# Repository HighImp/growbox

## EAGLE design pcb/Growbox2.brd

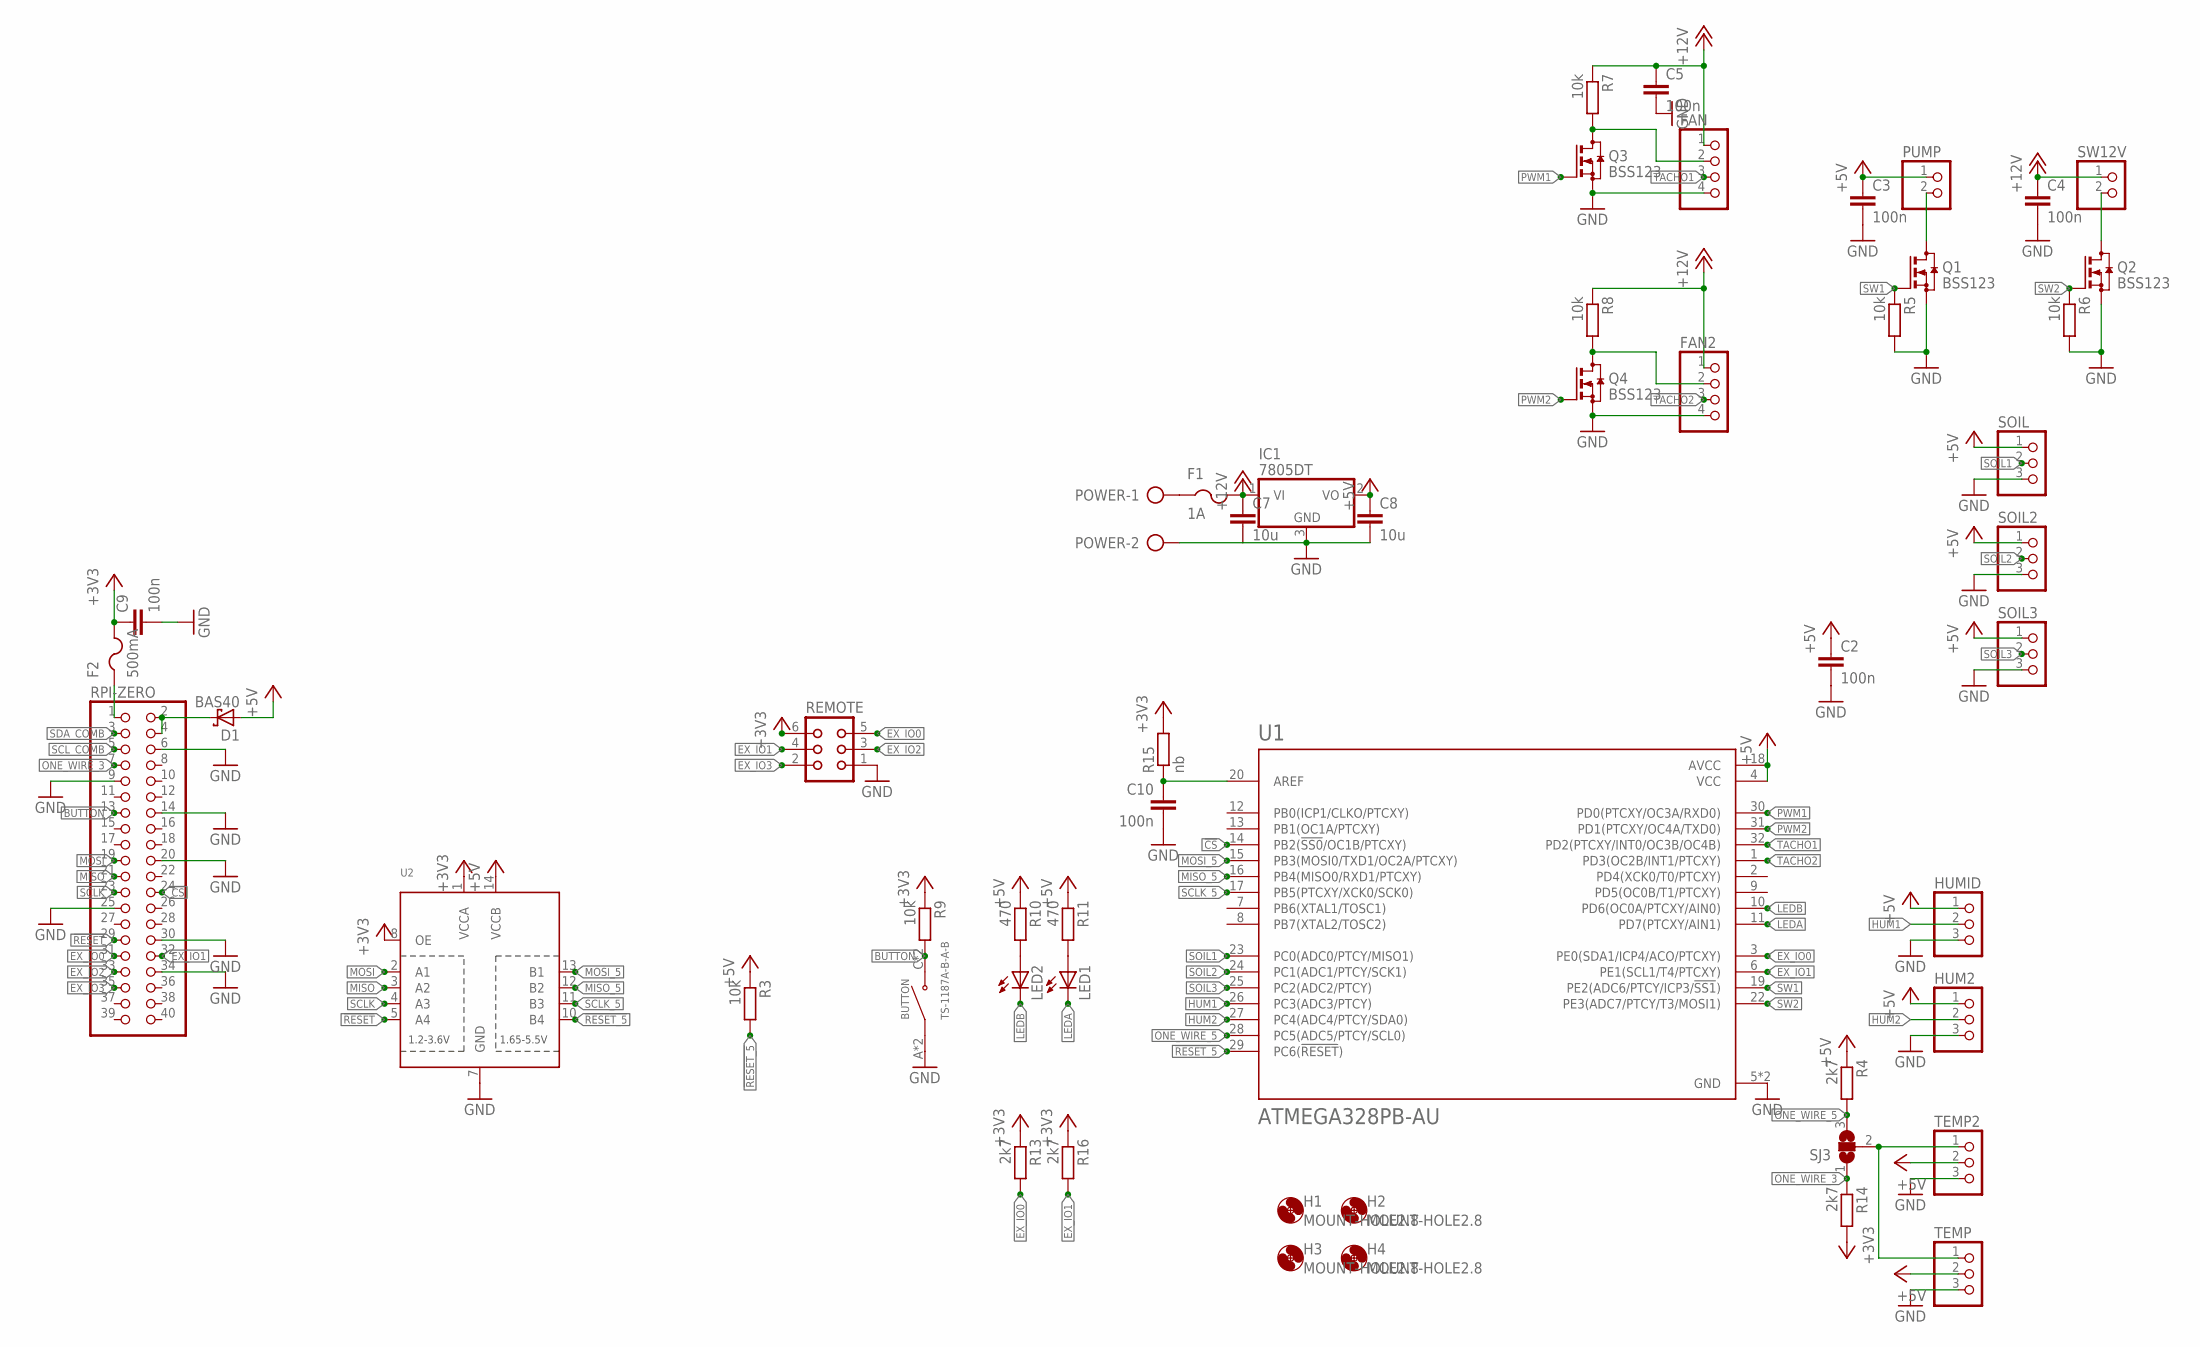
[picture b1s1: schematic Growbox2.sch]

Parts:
BUTTON: TS-1187A-B-A-B; SW_TS-1187A-B-A-B
C2, C3, C4, C5, C9, C10: 100n; C0603
C7, C8: 10u; C0603
D1: BAS40; SOT23
F1: 1A; R1206
F2: 500mA; R1206
FAN, FAN2: PINHD-1X4; 1X04
H1, H2, H3, H4: MOUNT-HOLE2.8; 2,8
HUM2: PINHD-1X3; 1X03
HUMID: PINHD-1X3; 1X03
IC1: 7805DT; TO252
LED1, LED2: LEDCHIP-LED0603; CHIP-LED0603
POWER: AK300/2
PUMP: PINHD-1X2; 1X02
Q1, Q2, Q3, Q4: BSS123; SOT23
R3, R5, R6, R7, R8, R9: 10k; R0603
R4, R13, R14, R16: 2k7; R0603
R10, R11: 470; R0603
R15: nb; R0603
REMOTE: CON06
RPI-ZERO: PINHD-2X20; 2X20
SJ3: SJ2W; SJ_2
SOIL, SOIL2, SOIL3: PINHD-1X3; 1X03
SW12V: PINHD-1X2; 1X02
TEMP, TEMP2: PINHD-1X3; 1X03
U1: ATMEGA328PB-AU; QFP80P900X900X120-32N
U2: TXB0104PWR; TSSOP14

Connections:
!CS: RPI-ZERO.24, U1.14 (PB2(!SS0!/OC1B/PTCXY))
!RESET: RPI-ZERO.29, U2.5 (A4)
!RESET_5: R3.2, U1.29 (PC6(!RESET!)), U2.10 (B4)
+3V3: C9.1, F2.2, R9.1, R13.1, R14.2, R15.2, R16.1, REMOTE.6, U2.1 (VCCA), U2.8 (OE)
+5V: C2.1, C3.1, C8.1, D1.1 (A), HUM2.1, HUMID.1, IC1.2 (VO), PUMP.1, R3.1, R4.1, R10.1, R11.1, SOIL.1, SOIL2.1, SOIL3.1, TEMP.2, TEMP2.2, U1.4 (VCC), U1.18 (AVCC), U2.14 (VCCB)
+12V: C4.1, C5.1, C7.1, F1.2, FAN.1, FAN2.1, IC1.1 (VI), R7.1, R8.1, SW12V.1
AREF: C10.1, R15.1, U1.20 (AREF)
BUTTON: BUTTON.C (NO), BUTTON.D (NO), R9.2, RPI-ZERO.13
EX_IO0: R13.2, REMOTE.5, RPI-ZERO.31, U1.3 (PE0(SDA1/ICP4/ACO/PTCXY))
EX_IO1: R16.2, REMOTE.4, RPI-ZERO.32, U1.6 (PE1(SCL1/T4/PTCXY))
EX_IO2: REMOTE.3, RPI-ZERO.33
EX_IO3: REMOTE.2, RPI-ZERO.35
GND: BUTTON.A (COM), BUTTON.B (COM), C2.2, C3.2, C4.2, C5.2, C7.2, C8.2, C9.2, C10.2, FAN.4, FAN2.4, HUM2.3, HUMID.3, IC1.3 (GND), POWER.2, Q1.2 (S), Q2.2 (S), Q3.2 (S), Q4.2 (S), R5.2, R6.2, REMOTE.1, RPI-ZERO.6, RPI-ZERO.9, RPI-ZERO.14, RPI-ZERO.20, RPI-ZERO.25, RPI-ZERO.30, RPI-ZERO.34, SOIL.3, SOIL2.3, SOIL3.3, TEMP.3, TEMP2.3, U1.5 (GND), U1.21 (GND), U2.7 (GND)
HUM1: HUMID.2, U1.26 (PC3(ADC3/PTCY))
HUM2: HUM2.2, U1.27 (PC4(ADC4/PTCY/SDA0))
LEDA: LED1.C, U1.11 (PD7(PTCXY/AIN1))
LEDB: LED2.C, U1.10 (PD6(OC0A/PTCXY/AIN0))
MISO: RPI-ZERO.21, U2.3 (A2)
MISO_5: U1.16 (PB4(MISO0/RXD1/PTCXY)), U2.12 (B2)
MOSI: RPI-ZERO.19, U2.2 (A1)
MOSI_5: U1.15 (PB3(MOSI0/TXD1/OC2A/PTCXY)), U2.13 (B1)
unnamed: F1.1, POWER.1
unnamed: F2.1, RPI-ZERO.1
unnamed: LED2.A, R10.2
unnamed: D1.3 (C), RPI-ZERO.2, RPI-ZERO.4
unnamed: LED1.A, R11.2
ONE_WIRE: SJ3.2, TEMP.1, TEMP2.1
ONE_WIRE_3: R14.1, RPI-ZERO.7, SJ3.1
ONE_WIRE_5: R4.2, SJ3.3, U1.28 (PC5(ADC5/PTCY/SCL0))
PWM1: Q3.1 (G), U1.30 (PD0(PTCXY/OC3A/RXD0))
PWM1_SIG: FAN.2, Q3.3 (D), R7.2
PWM2: Q4.1 (G), U1.31 (PD1(PTCXY/OC4A/TXD0))
PWM2_SIG: FAN2.2, Q4.3 (D), R8.2
SCLK: RPI-ZERO.23, U2.4 (A3)
SCLK_5: U1.17 (PB5(PTCXY/XCK0/SCK0)), U2.11 (B3)
SCL_COMB: RPI-ZERO.5
SDA_COMB: RPI-ZERO.3
SOIL1: SOIL.2, U1.23 (PC0(ADC0/PTCY/MISO1))
SOIL2: SOIL2.2, U1.24 (PC1(ADC1/PTCY/SCK1))
SOIL3: SOIL3.2, U1.25 (PC2(ADC2/PTCY))
SW1: Q1.1 (G), R5.1, U1.19 (PE2(ADC6/PTCY/ICP3/!SS1!))
SW1_NEG: PUMP.2, Q1.3 (D)
SW2: Q2.1 (G), R6.1, U1.22 (PE3(ADC7/PTCY/T3/MOSI1))
SW2_NEG: Q2.3 (D), SW12V.2
TACHO1: FAN.3, U1.32 (PD2(PTCXY/INT0/OC3B/OC4B))
TACHO2: FAN2.3, U1.1 (PD3(OC2B/INT1/PTCXY))

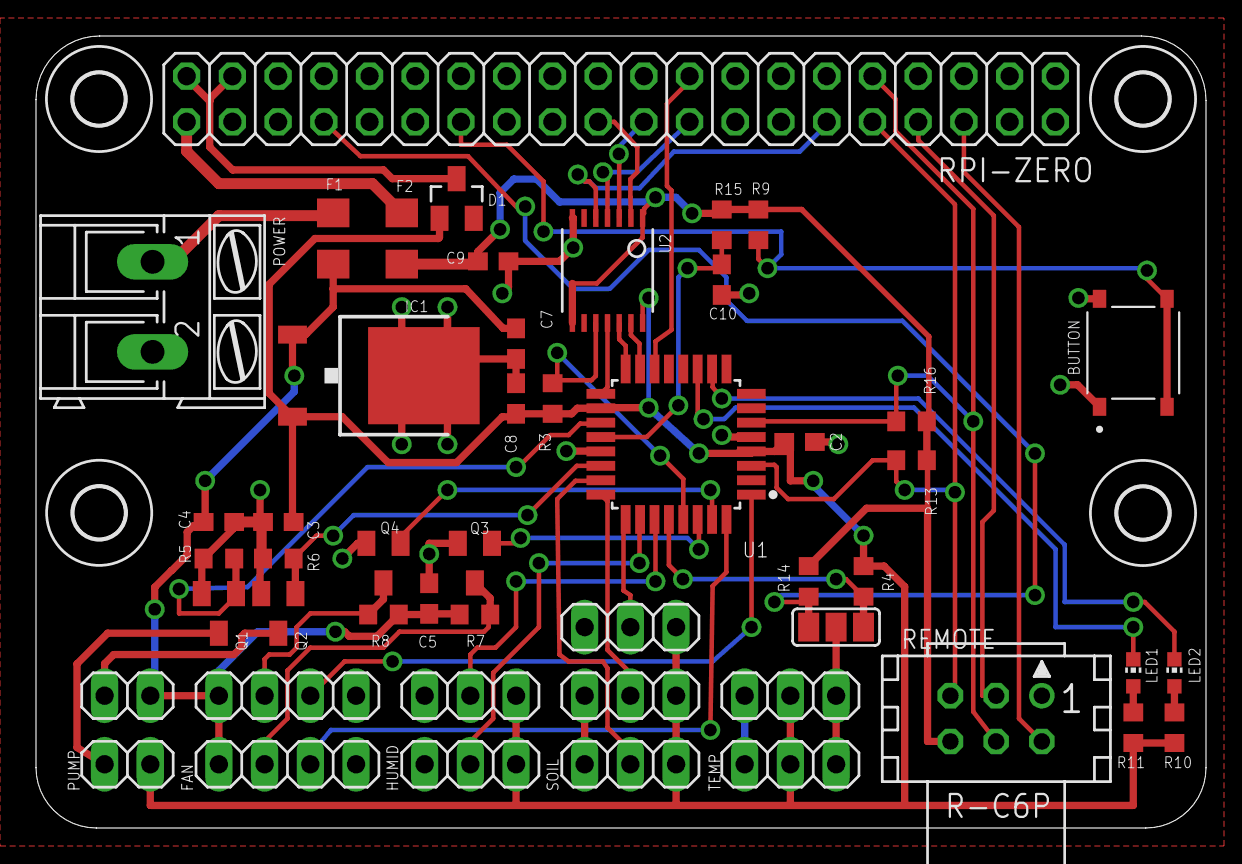
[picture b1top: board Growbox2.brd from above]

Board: 2 copper layers, 65.0 x 44.0 mm, 53 parts (0 on the bottom side), 44 nets.

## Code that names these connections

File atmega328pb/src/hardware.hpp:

#include <inttypes.h>

#ifndef _HARDWARE_H
#define _HARDWARE_H

// ANALOG PINS
const char SOIL1 = A0; // PC0
const char SOIL2 = A1; // PC1
const char SOIL3 = A2; // PC2

// BUS_PINS
const char HUM1 = 17; // PC3
const char HUM2 = 18; // PC4
const uint8_t ONE_WIRE = 19; // PC5

// FAN_PINS
const uint8_t PWM1 = 0; // PD0
const uint8_t PWM2 = 1; // PD1
const uint8_t TACHO1 = 2; // PD2
const uint8_t TACHO2 = 3; // PD3

// LED PINS
const uint8_t LEDB = 6; // PD6
const uint8_t LEDA = 7; // PD7

// SWITCH_PINS
const uint8_t SWITCH1 = 25; // PE2
const uint8_t SWITCH2 = 26; // PE3

// DIRECT_COM_PINS
const uint8_t EX_IO1 = 23; // PE0
const uint8_t EX_IO2 = 24; // PE1

# endif

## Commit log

2024-06-14 add simple remote deployment
2024-06-16 first working spi version
2024-06-19 WORKING
